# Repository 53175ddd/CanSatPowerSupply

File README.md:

# CanSatPowerSupply

缶サット用自作マイコンボード向け電源ユニット  
CR2032 または LIR2032 が使用できます  
LIR2032 使用時，外部電源入力に 5V を供給することで 10mA 定電流ダイオードと 3.9V 定電圧ダイオードでの簡易 CCCV 充電が可能です

また，電源電圧監視用 ADC 入力が可能で，GPIO32 ~ GPIO35 を入力として選択可能です

# 部品表

| 部品番号 | 部品名 | 秋月 |
|----|----|----|
| BT1 | バッテリホルダ | <https://akizukidenshi.com/catalog/g/g111348/> |
| C1 ~ C3 | 1uF 0603-1608M | <https://akizukidenshi.com/catalog/g/g114526/> |
| C4 | 10uF 0603-1608M | <https://akizukidenshi.com/catalog/g/g113161/> |
| D1, D2 | 1N4148 | <https://akizukidenshi.com/catalog/g/g100941/> |
| D3 | 定電流ダイオード 10mA | <https://akizukidenshi.com/catalog/g/g100185/> |
| D4 | 定電圧ダイオード 3.9V | <https://akizukidenshi.com/catalog/g/g108710/> |
| J1 ~ J3 | 分割ロングピンソケット | <https://akizukidenshi.com/catalog/g/g105779/> |
| SW1 | SPDT スイッチ | <https://akizukidenshi.com/catalog/g/g115703/> |
| U1 | LTC3245 | <https://akizukidenshi.com/catalog/g/g108177/> |

# ギャラリー

部品実装イメージ

回路図

CAD イメージ

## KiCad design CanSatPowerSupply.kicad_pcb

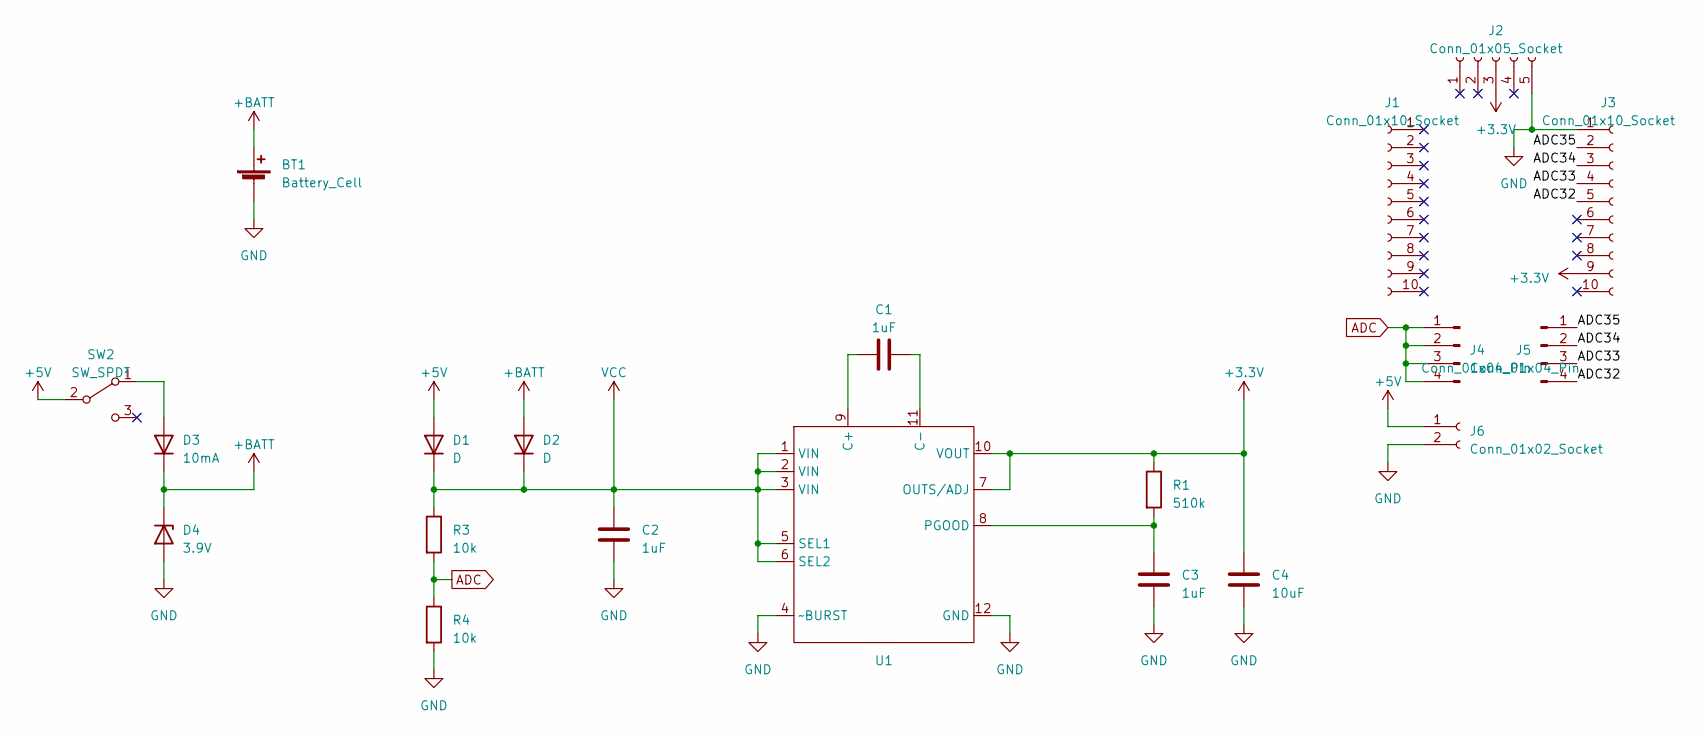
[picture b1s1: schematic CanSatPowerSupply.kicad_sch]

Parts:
BT1: Battery_Cell; BatteryHolder_Keystone_1060_1x2032
C1, C2, C3: 1uF; C_0603_1608Metric
C4: 10uF; C_0603_1608Metric
D1, D2: D; D_T-1_P5.08mm_Horizontal
D3: 10mA; D_T-1_P5.08mm_Horizontal
D4: 3.9V; D_T-1_P5.08mm_Horizontal
J1, J3: Conn_01x10_Socket; PinSocket_1x10_P2.54mm_Vertical
J2: Conn_01x05_Socket; PinSocket_1x05_P2.54mm_Vertical
J4, J5: Conn_01x04_Pin; PinSocket_1x04_P2.54mm_Vertical
J6: Conn_01x02_Socket; PinSocket_1x02_P2.54mm_Vertical
R1: 510k; R_0603_1608Metric
R3, R4: 10k; R_0603_1608Metric
SW2: SW_SPDT; SW_CuK_OS102011MA1QN1_SPDT_Angled
U1: MSOP-12_3x4mm_P0.65mm

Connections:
+3.3V: C4.1, J2.3, J3.9, R1.1, U1.7 (OUTS/ADJ), U1.10 (VOUT)
+5V: D1.2 (A), J6.1, SW2.2 (B); also elsewhere on the board
+BATT: BT1.1 (+), D2.2 (A), D3.1 (K), D4.1 (K)
/ADC32: J3.5, J5.4
/ADC33: J3.4, J5.3
/ADC34: J3.3, J5.2
/ADC35: J3.2, J5.1
ADC: J4.1, J4.2, J4.3, J4.4, R3.2, R4.1
GND: BT1.2 (-), C2.2, C3.2, C4.2, D4.2 (A), J2.5, J3.1, J6.2, R4.2, U1.4 (~BURST), U1.12 (GND)
unnamed 9: D3.2 (A), SW2.1 (A); also elsewhere on the board
unnamed: C1.1, U1.9 (C+)
unnamed: C1.2, U1.11 (C-)
unnamed: C3.1, R1.2, U1.8 (PGOOD)
VCC: C2.1, D1.1 (K), D2.1 (K), R3.1, U1.1 (VIN), U1.2 (VIN), U1.3 (VIN), U1.5 (SEL1), U1.6 (SEL2)

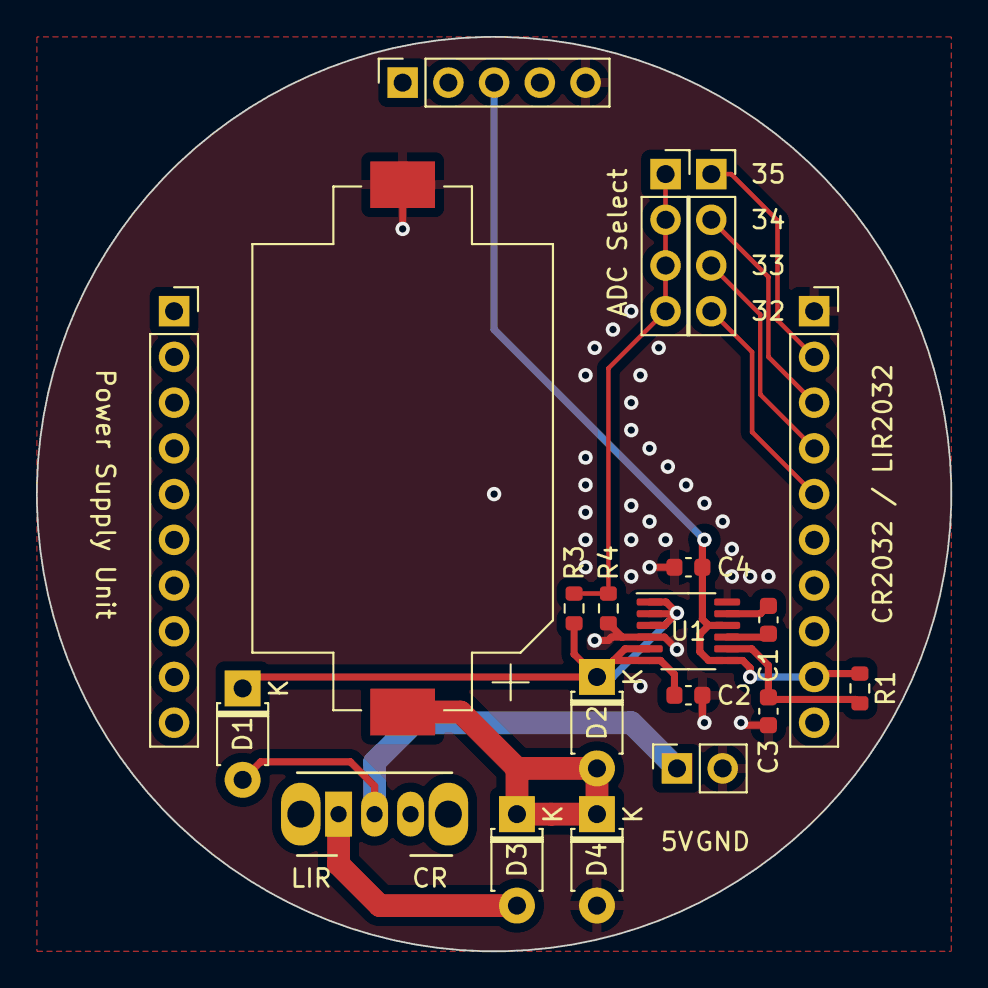
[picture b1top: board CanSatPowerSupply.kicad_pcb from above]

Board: 2 copper layers, 50.8 x 50.8 mm, 20 parts (0 on the bottom side), 14 nets.

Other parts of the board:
SW1: SW_SPDT; SW_CuK_OS102011MA1QN1_SPDT_Angled

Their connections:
+5V: SW1.2 (B); also elsewhere on the board
unnamed 9: SW1.1 (A); also elsewhere on the board

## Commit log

2024-03-24 説明書き追加
2024-03-24 体裁調整
2024-03-24 部品表追記
